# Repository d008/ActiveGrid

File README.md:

# ActiveGrid
winglet_body.sldprt -- SolidWorks CAD files for the winglet body

winglet_lid.sldprt -- SolidWorks CAD files for the winglet lid 

winglet.brd|winglet.sch -- Eagle CAD files for the winglet PCB 

power.brd|power.sch -- Eagle CAD files for consolidating the power to each winglet at the bottom of the grid (capacity for 8 winglets each)

main.ino -- Arduino code to be uploaded onto each winglet's ESP8266

active_grid.m -- example of complementary Matlab code to drive the winglets

AG_parts_list -- list of parts and estimated budget 

Active Grid Quick Start Guide -- Instructions for running the active grid

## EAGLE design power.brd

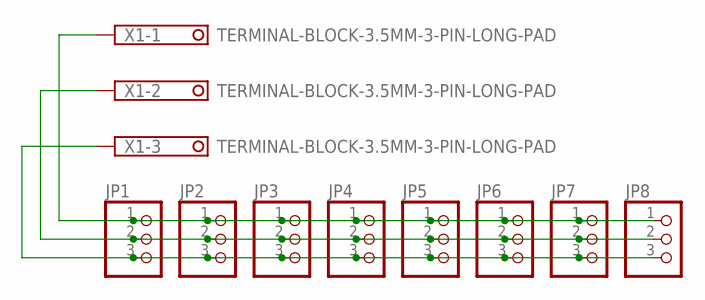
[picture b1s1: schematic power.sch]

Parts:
JP1, JP2, JP3, JP4, JP5, JP6, JP7, JP8: PINHD-1X3/90; 1X03/90
X1: TERMINAL-BLOCK-3.5MM-3-PIN-LONG-PAD; TERMINAL-BLOCK-3-PIN-3.5MM-LONG-PAD

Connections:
unnamed: JP1.1, JP2.1, JP3.1, JP4.1, JP5.1, JP6.1, JP7.1, JP8.1, X1.1
unnamed: JP1.2, JP2.2, JP3.2, JP4.2, JP5.2, JP6.2, JP7.2, JP8.2, X1.2
unnamed: JP1.3, JP2.3, JP3.3, JP4.3, JP5.3, JP6.3, JP7.3, JP8.3, X1.3

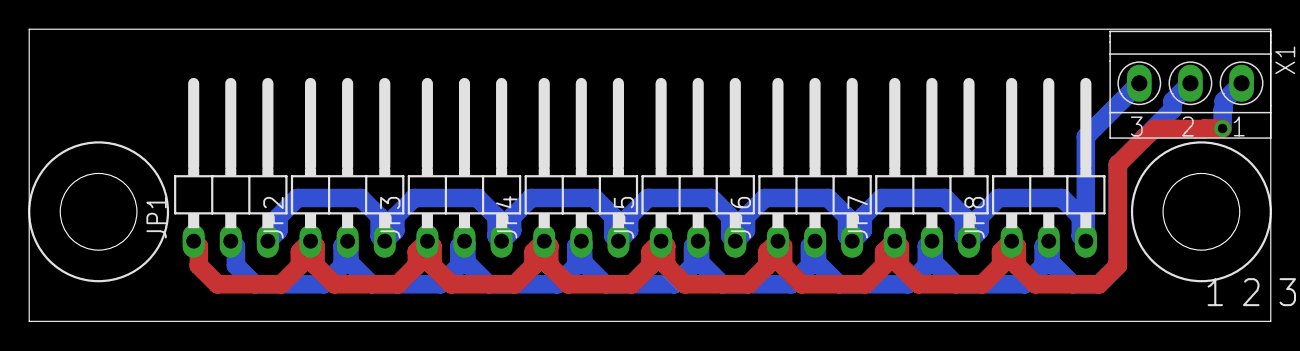
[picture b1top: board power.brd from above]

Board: 2 copper layers, 85.0 x 20.0 mm, 9 parts (0 on the bottom side), 3 nets.

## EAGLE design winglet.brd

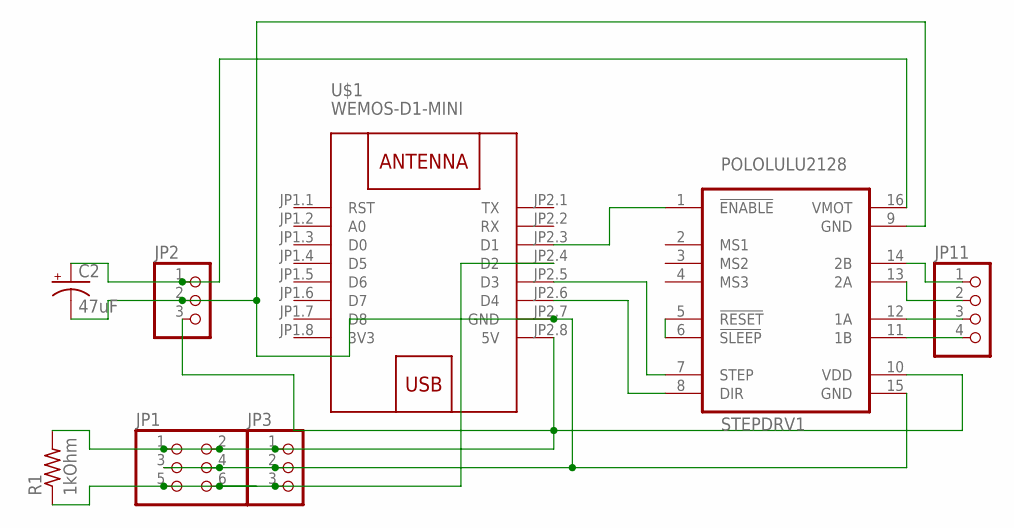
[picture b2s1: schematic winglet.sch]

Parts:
C2: 47uF; PANASONIC_D
JP1: PINHD-2X3; 2X03
JP2: PINHD-1X3/90; 1X03/90
JP3: PINHD-1X3; 1X03
JP11: PINHD-1X4/90; 1X04/90
R1: 1kOhm; M1206
STEPDRV1: POLOLULU2128
U$1: WEMOS-D1-MINI

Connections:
3V3: U$1.JP1.8 (3V3)
unnamed: JP1.1, JP1.2, JP2.3, JP3.1, R1.2, STEPDRV1.10 (VDD), U$1.JP2.8 (5V)
unnamed: C2.-, JP1.3, JP1.4, JP2.2, JP3.2, STEPDRV1.9 (GND), STEPDRV1.15 (GND), U$1.JP2.7 (GND)
unnamed: JP1.5, JP1.6, JP3.3, R1.1, U$1.JP2.4 (D2)
unnamed: STEPDRV1.5 (!RESET), STEPDRV1.6 (!SLEEP)
unnamed: STEPDRV1.1 (!ENABLE), U$1.JP2.3 (D1)
unnamed: STEPDRV1.7 (STEP), U$1.JP2.5 (D3)
unnamed: C2.+, JP2.1, STEPDRV1.16 (VMOT)
unnamed: STEPDRV1.8 (DIR), U$1.JP2.6 (D4)
unnamed: JP11.4, STEPDRV1.11 (1B)
unnamed: JP11.3, STEPDRV1.12 (1A)
unnamed: JP11.2, STEPDRV1.13 (2A)
unnamed: JP11.1, STEPDRV1.14 (2B)

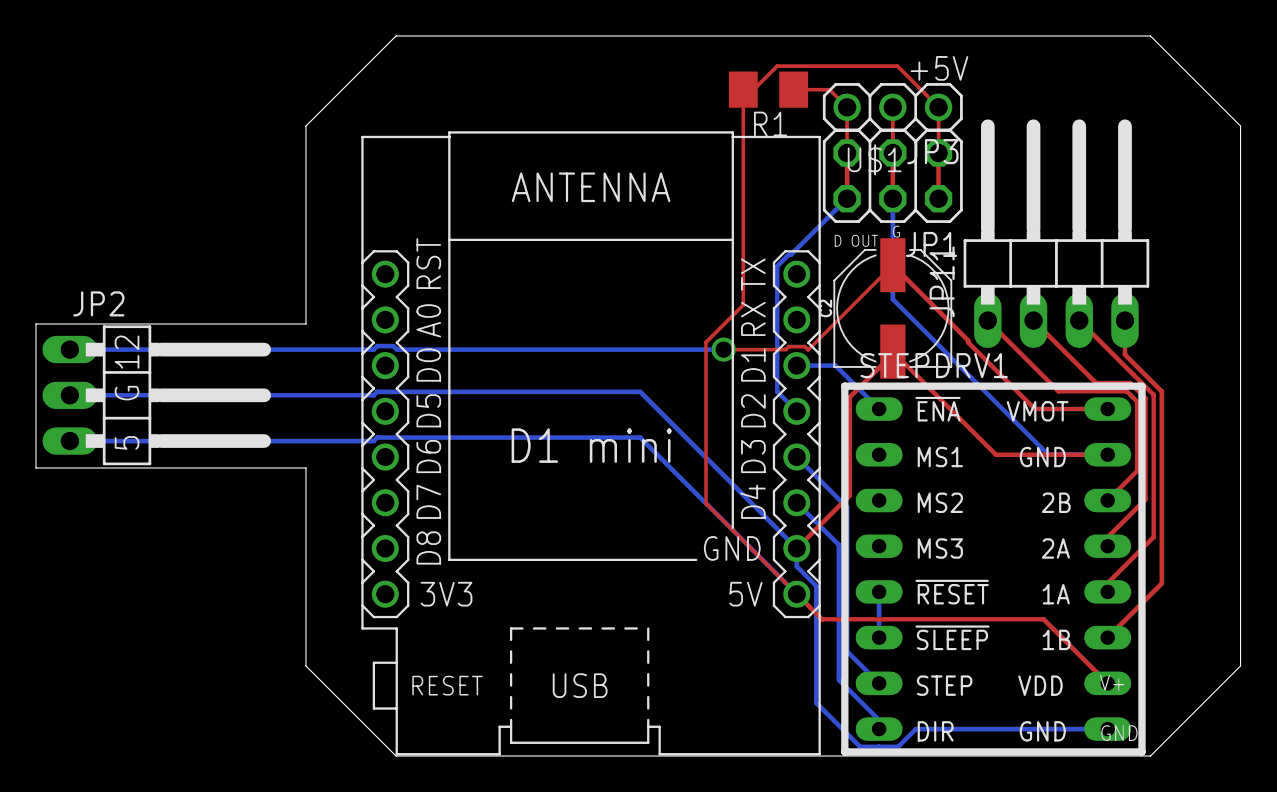
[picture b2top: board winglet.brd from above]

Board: 2 copper layers, 66.9 x 40.0 mm, 8 parts (0 on the bottom side), 12 nets.

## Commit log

2021-04-19 Rename Trey.ino to old/Trey.ino
2021-04-19 Rename Trey.m to old/Trey.m

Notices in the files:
parts and their libraries:
diy-modules: Released under the Creative Commons Attribution 4.0 International License: http://creativecommons.org/licenses/by/4.0
SparkFun-Capacitors: Licensing: Creative Commons ShareAlike 4.0 International - https://creativecommons.org/licenses/by-sa/4.0
